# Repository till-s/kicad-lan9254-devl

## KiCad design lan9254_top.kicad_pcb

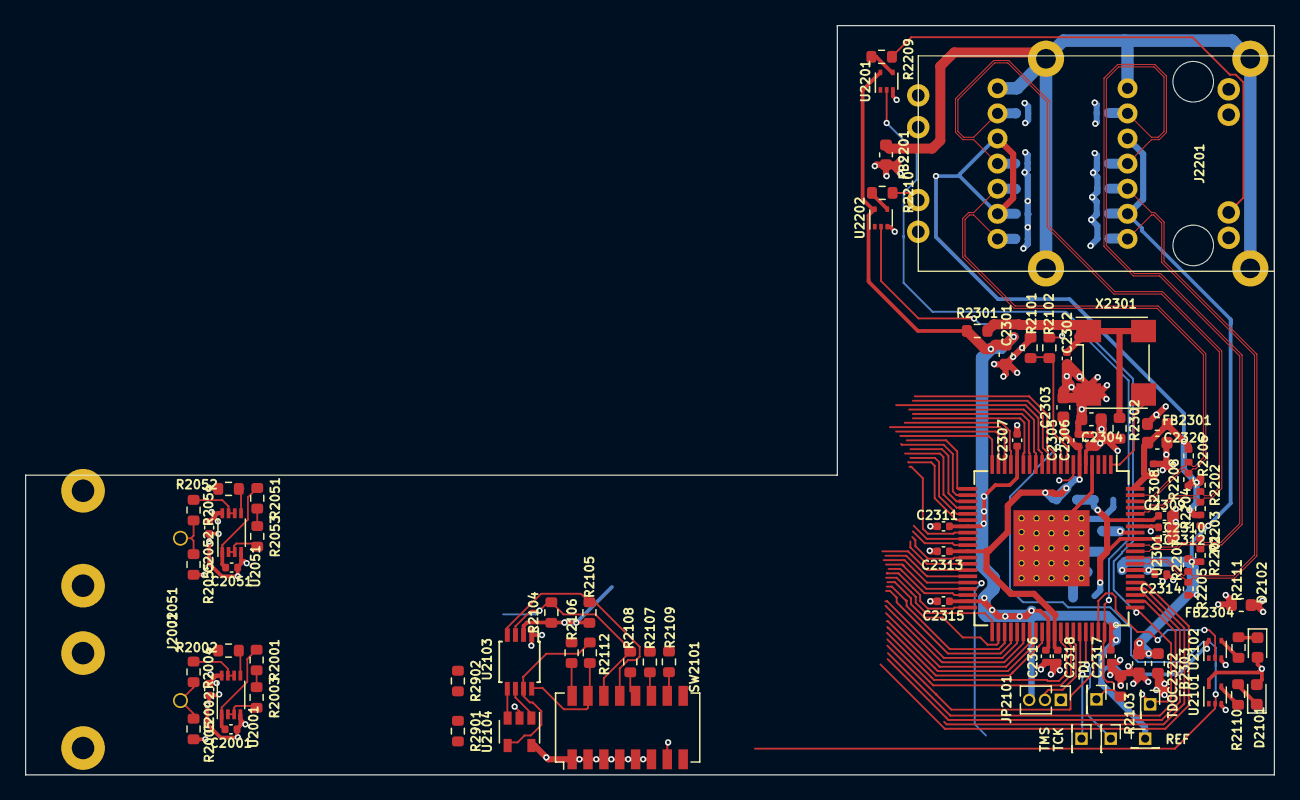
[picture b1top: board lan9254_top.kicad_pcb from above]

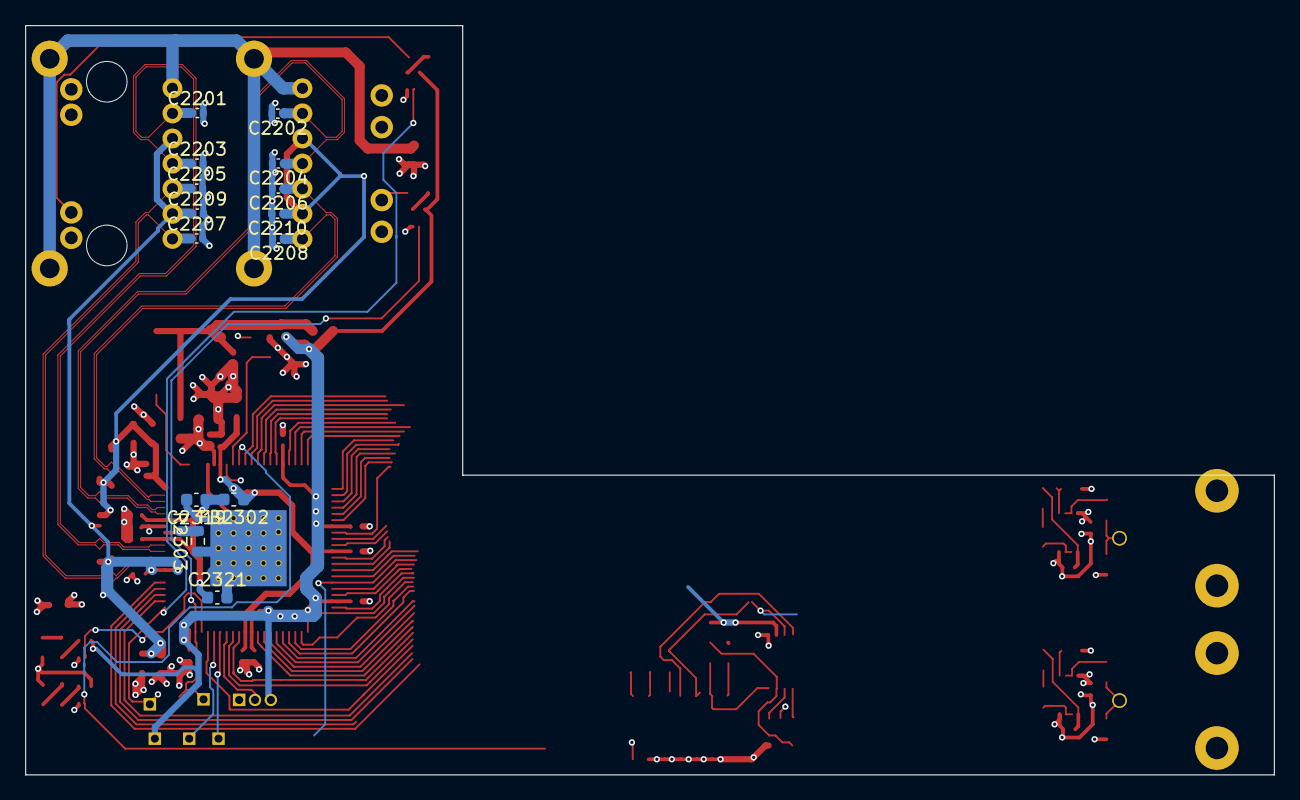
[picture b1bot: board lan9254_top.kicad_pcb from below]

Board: 4 copper layers, 100.0 x 60.0 mm, 100 parts (14 on the bottom side), 54 nets.

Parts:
C2001, C2002, C2051, C2052, C2302, C2306, C2307, C2308, C2309, C2310, C2311, C2312, C2313, C2314, C2315, C2316, C2317, C2318: 100n; C_0402_1005Metric
C2201, C2202, C2203, C2204, C2205, C2206, C2207, C2208, C2209, C2210: 10p; C_0402_1005Metric
C2301, C2303, C2304: 1u_loESR; C_0603_1608Metric
C2305: 470p; C_0402_1005Metric
C2319, C2320, C2321, C2322: 1u; C_0603_1608Metric
D2101, D2102: LED_Small; LED_0603_1608Metric
FB2201, FB2301, FB2302, FB2303, FB2304: FB_250; L_0603_1608Metric
J2001, J2051: BNC; BNC_Molex_0731713150
J2201: BEL_0845_2G1T_H5; BEL_0845-2G1T-H5
JP2101: Jumper_3_Bridged12; PinHeader_1x03_P1.27mm_Vertical
R2001, R2005, R2051, R2055: 100k; R_0603_1608Metric
R2002, R2052: 2k2; R_0603_1608Metric
R2003, R2053, R2110, R2111, R2209, R2210: 100; R_0603_1608Metric
R2004, R2054, R2301, R2302: 0; R_0603_1608Metric
R2101, R2102, R2103, R2106, R2107, R2108: 1k; R_0603_1608Metric
R2104, R2105, R2112, R2901, R2902: 10k; R_0603_1608Metric
R2109: 4k7; R_0603_1608Metric
R2201, R2202, R2203, R2204, R2205, R2206, R2207, R2208: 50; R_0402_1005Metric
R2303: 12.1k; R_0603_1608Metric
SW2101: SW_DIP_x08; SW_DIP_SPSTx08_Slide_Copal_CHS-08A_W5.08mm_P1.27mm_JPin
TP2301: TDO; PinHeader_1x01_P1.27mm_Vertical
TP2302: TDI; PinHeader_1x01_P1.27mm_Vertical
TP2303: TCK; PinHeader_1x01_P1.27mm_Vertical
TP2304: TMS; PinHeader_1x01_P1.27mm_Vertical
TP2305: REF; PinHeader_1x01_P1.27mm_Vertical
U2001, U2051: 74LVC2T45DC; VSSOP-8_2.3x2mm_P0.5mm
U2101, U2102, U2201, U2202: 74LVC1G06; SOT-553
U2103: PCA9306; TSSOP-8_3x3mm_P0.65mm
U2104: 24AA0x; SOT-23-5
U2301: lan9254; TQFP-80_12x12mm_P0.5mm_EP6x6mm
X2301: FNETHE025; Oscillator_SMD_Diodes_FN-4Pin_7.0x5.0mm

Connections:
+1V8_lan9254: C2001.1, C2051.1, C2301.1, C2307.1, C2311.1, C2315.1, C2316.1, C2317.1, JP2101.3, R2001.1, R2051.1, R2104.1, R2105.1, R2301.1, TP2305.1, U2001.1, U2051.1, U2102.5, U2103.2, U2201.5, U2202.5, U2301.16, U2301.27, U2301.39, U2301.50, U2301.60
+3V3_lan9254: C2002.1, C2052.1, C2304.1, C2306.1, D2101.2, D2102.2, FB2301.1, FB2303.1, FB2304.1, J2201.15, J2201.19, R2102.2, R2302.1, SW2101.7, U2001.8, U2051.8, U2101.5, U2301.5, U2301.7
+3V3_lan9254_iic: R2112.1, R2901.1, R2902.1, U2103.7, U2104.4
/lan9254/EESCL: R2104.2, R2108.1, SW2101.14, TP2303.1, U2102.2, U2103.3, U2301.56, U2301.58
/lan9254/EESDA: R2105.2, SW2101.13, TP2304.1, U2103.4, U2301.55
/lan9254/ERRLED: R2109.1, U2101.2, U2301.9
/lan9254/FPGA_23: R2106.1, U2301.36
/lan9254/FPGA_IO1_DAT: R2001.2, R2003.1
/lan9254/FPGA_IO1_DIR: R2002.1, U2001.5
/lan9254/FPGA_IO2_DAT: R2051.2, R2053.1
/lan9254/FPGA_IO2_DIR: R2052.1, U2051.5
/lan9254/LINKACT0: R2107.1, TP2301.1, U2201.2, U2301.61
/lan9254/LINKACT1: R2103.1, TP2302.1, U2202.2, U2301.59
/lan9254/SCL_3V3: R2901.2, U2103.6, U2104.1
/lan9254/SDA_3V3: R2902.2, U2103.5, U2104.3
/lan9254/TESTMODE: JP2101.2, U2301.54
/lan9254/VDD12TX12: C2309.2, C2312.2, C2319.1, C2321.1, FB2302.2, U2301.72, U2301.75
/lan9254/VDD33BIAS: C2310.2, FB2304.2, U2301.74
/lan9254/VDD33TXRX1: C2209.1, C2314.2, C2322.1, FB2303.2, J2201.2, J2201.5, R2201.1, R2203.1, R2205.1, R2207.1, U2301.67
/lan9254/VDD33TXRX2: C2210.1, C2308.2, C2320.1, FB2301.2, J2201.9, J2201.12, R2202.1, R2204.1, R2206.1, R2208.1, U2301.80
/lan9254/VDDCR: C2303.1, C2305.1, C2313.1, C2318.1, FB2302.1, U2301.6, U2301.31, U2301.51
/lan9254/XTAL_MODE: R2101.1, R2102.1, U2301.8
/lan9254/rj45_ports/P0_RXD_N: C2201.1, J2201.6, R2201.2, U2301.70
/lan9254/rj45_ports/P0_RXD_P: C2203.1, J2201.4, R2203.2, U2301.71
/lan9254/rj45_ports/P0_TXD_N: C2205.1, J2201.3, R2205.2, U2301.68
/lan9254/rj45_ports/P0_TXD_P: C2207.1, J2201.1, R2207.2, U2301.69
/lan9254/rj45_ports/P1_RXD_N: C2202.1, J2201.13, R2202.2, U2301.77
/lan9254/rj45_ports/P1_RXD_P: C2204.1, J2201.11, R2204.2, U2301.76
/lan9254/rj45_ports/P1_TXD_N: C2206.1, J2201.10, R2206.2, U2301.79
/lan9254/rj45_ports/P1_TXD_P: C2208.1, J2201.8, R2208.2, U2301.78
GND_lan9254: C2001.2, C2002.2, C2051.2, C2052.2, C2201.2, C2202.2, C2203.2, C2204.2, C2205.2, C2206.2, C2207.2, C2208.2, C2209.2, C2210.2, C2301.2, C2302.2, C2303.2, C2304.2, C2305.2, C2306.2, C2307.2, C2308.1, C2309.1, C2310.1, C2311.2, C2312.1, C2313.2, C2314.1, C2315.2, C2316.2, C2317.2, C2318.2, C2319.2, C2320.2, C2321.2, C2322.2, FB2201.2, J2001.2, J2051.2, JP2101.1, R2002.2, R2005.2, R2052.2, R2055.2, R2101.2, R2103.2, R2303.1, SW2101.1, SW2101.2, SW2101.3, SW2101.4, SW2101.5, SW2101.6, U2001.4, U2051.4, U2101.3, U2102.3, U2103.1, U2104.2, U2104.5, U2201.3, U2202.3, U2301.4, U2301.81, X2301.2
unnamed: C2302.1, R2301.2, R2302.2, X2301.1, X2301.4
unnamed: D2101.1, R2110.1
unnamed: D2102.1, R2111.1
unnamed: FB2201.1, J2201.7, J2201.14, J2201.SH
unnamed: J2001.1, R2004.2, R2005.1
unnamed: J2051.1, R2054.2, R2055.1
unnamed: J2201.16, R2209.1
unnamed: J2201.20, R2210.1
unnamed: R2003.2, U2001.2, U2001.3
unnamed: R2004.1, U2001.6, U2001.7
unnamed: R2053.2, U2051.2, U2051.3
unnamed: R2054.1, U2051.6, U2051.7
unnamed: R2106.2, SW2101.16
unnamed: R2107.2, SW2101.11
unnamed: R2108.2, SW2101.12
unnamed: R2109.2, SW2101.10
unnamed: R2110.2, U2101.4
unnamed: R2111.2, U2102.4
unnamed: R2112.2, SW2101.15, U2103.8
unnamed: R2209.2, U2201.4
unnamed: R2210.2, U2202.4
unnamed: R2303.2, U2301.73
unnamed: U2301.1, X2301.3

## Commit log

2021-06-30 gitification
2021-07-06 added I/O connectors, JTAG (just in case) and more
2021-07-06 updated PCB from schematic, updated footprints from libs
2021-07-06 reannotated for merging with te0715 development board
2021-07-06 moved PCB to not overlap with te0715 base board
2021-07-06 reannotated top-module and updated PCB (prior to merging with base-board)
2021-07-06 annotated from te0725 dev-base board
2021-07-06 reduced default netclass clearance from 8mil to 6mil to match base-board setup
2021-07-06 renamed diff-pair netclass diffp->diffp_ec due to mis-match with base-board setup
2021-07-07 fixed i2c switch (Vref2 is *not* a normal power input); small fixes
2021-07-07 added more component values/part numbers
2021-07-20 some fixes; don't recall details :-(
2022-02-02 WIP save
2022-02-10 changed LED drivers; added Jumpers, write-protect
    Modified LED drivers (XOR approach) to work with lan9254's
    open-drain/-source outputs.
    Routed spare switches as jumpers out of this module.
    Route eeprom-write protect out of this module.
    Route eeprom-isolation switch info out (so that FPGA may easily
    determine whether EEPROM emulation is used or not).
2022-04-28 further work...
2022-05-02 added 3rd GPIO
2022-05-05 Added pull-up resistor to #RST line
    Optional - just to be safe. The doc says we shouldn't rely on
    the internal pull-up driving external loads.
2022-05-05 updated cap footprint
2023-03-28 converted to kicad-6
2023-03-30 Basic layout done
2023-03-30 First layout done (no checks yet)
2023-04-02 work
